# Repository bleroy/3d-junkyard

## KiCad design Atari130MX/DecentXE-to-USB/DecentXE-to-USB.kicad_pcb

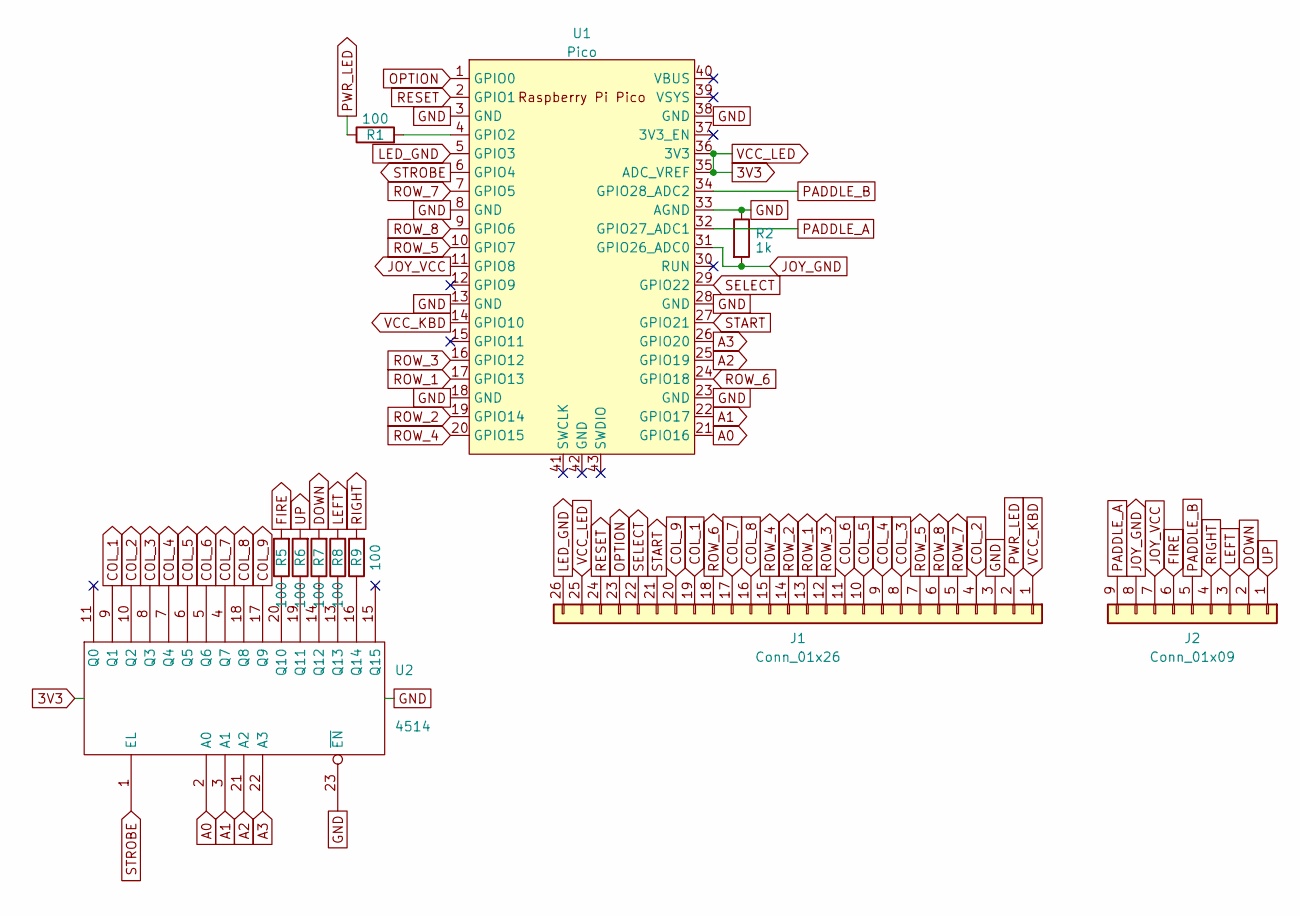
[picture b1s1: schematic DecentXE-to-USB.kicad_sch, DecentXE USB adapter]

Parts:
J1: Conn_01x26; Molex_200528-0260_1x26-1MP_P1.00mm_Horizontal
J2: Conn_01x09; DSUB-9_Male_Horizontal_P2.77x2.84mm_EdgePinOffset4.94mm_Hou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
R1, R5, R6, R7, R8, R9: 100; R_0603_1608Metric
R2: 1k; R_0603_1608Metric
U1: Pico; RPi_Pico_SMD_TH
U2: 4514; SOIC-24W_7.5x15.4mm_P1.27mm

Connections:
3V3: J1.25, U1.35 (ADC_VREF), U1.36 (3V3), U2.24 (Vdd)
A0: U1.21 (GPIO16), U2.2 (A0)
A1: U1.22 (GPIO17), U2.3 (A1)
A2: U1.25 (GPIO19), U2.21 (A2)
A3: U1.26 (GPIO20), U2.22 (A3)
COL_1: J1.19, U2.9 (Q1)
COL_2: J1.4, U2.10 (Q2)
COL_3: J1.8, U2.8 (Q3)
COL_4: J1.9, U2.7 (Q4)
COL_5: J1.10, U2.6 (Q5)
COL_6: J1.11, U2.5 (Q6)
COL_7: J1.17, U2.4 (Q7)
COL_8: J1.16, U2.18 (Q8)
COL_9: J1.20, U2.17 (Q9)
DOWN: J2.2, R7.2
FIRE: J2.6, R5.2
GND: J1.3, R2.1, U1.3 (GND), U1.8 (GND), U1.13 (GND), U1.18 (GND), U1.23 (GND), U1.28 (GND), U1.33 (AGND), U1.38 (GND), U2.12 (Vss), U2.23 (~EN)
JOY_GND: J2.8, R2.2, U1.31 (GPIO26_ADC0)
JOY_VCC: J2.7, U1.11 (GPIO8)
LED_GND: J1.26, U1.5 (GPIO3)
LEFT: J2.3, R8.2
unnamed: R1.2, U1.4 (GPIO2)
unnamed: R5.1, U2.20 (Q10)
unnamed: R6.1, U2.19 (Q11)
unnamed: R7.1, U2.14 (Q12)
unnamed: R8.1, U2.13 (Q13)
unnamed: R9.1, U2.16 (Q14)
OPTION: J1.23, U1.1 (GPIO0)
PADDLE_A: J2.9, U1.32 (GPIO27_ADC1)
PADDLE_B: J2.5, U1.34 (GPIO28_ADC2)
PWR_LED: J1.2, R1.1
RESET: J1.24, U1.2 (GPIO1)
RIGHT: J2.4, R9.2
ROW_1: J1.13, U1.17 (GPIO13)
ROW_2: J1.14, U1.19 (GPIO14)
ROW_3: J1.12, U1.16 (GPIO12)
ROW_4: J1.15, U1.20 (GPIO15)
ROW_5: J1.7, U1.10 (GPIO7)
ROW_6: J1.18, U1.24 (GPIO18)
ROW_7: J1.5, U1.7 (GPIO5)
ROW_8: J1.6, U1.9 (GPIO6)
SELECT: J1.22, U1.29 (GPIO22)
START: J1.21, U1.27 (GPIO21)
STROBE: U1.6 (GPIO4), U2.1 (EL)
UP: J2.1, R6.2
VCC_KBD: J1.1, U1.14 (GPIO10)

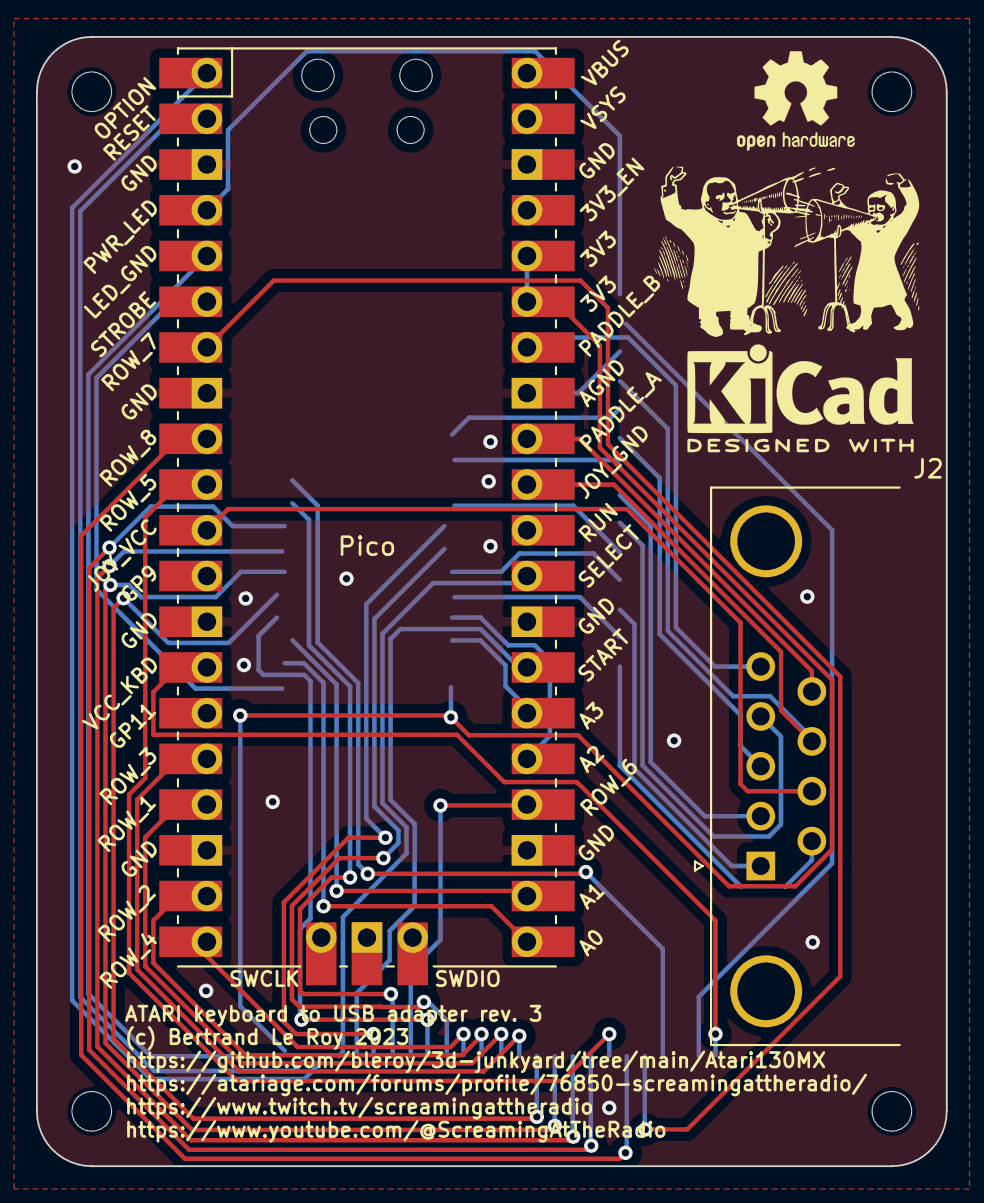
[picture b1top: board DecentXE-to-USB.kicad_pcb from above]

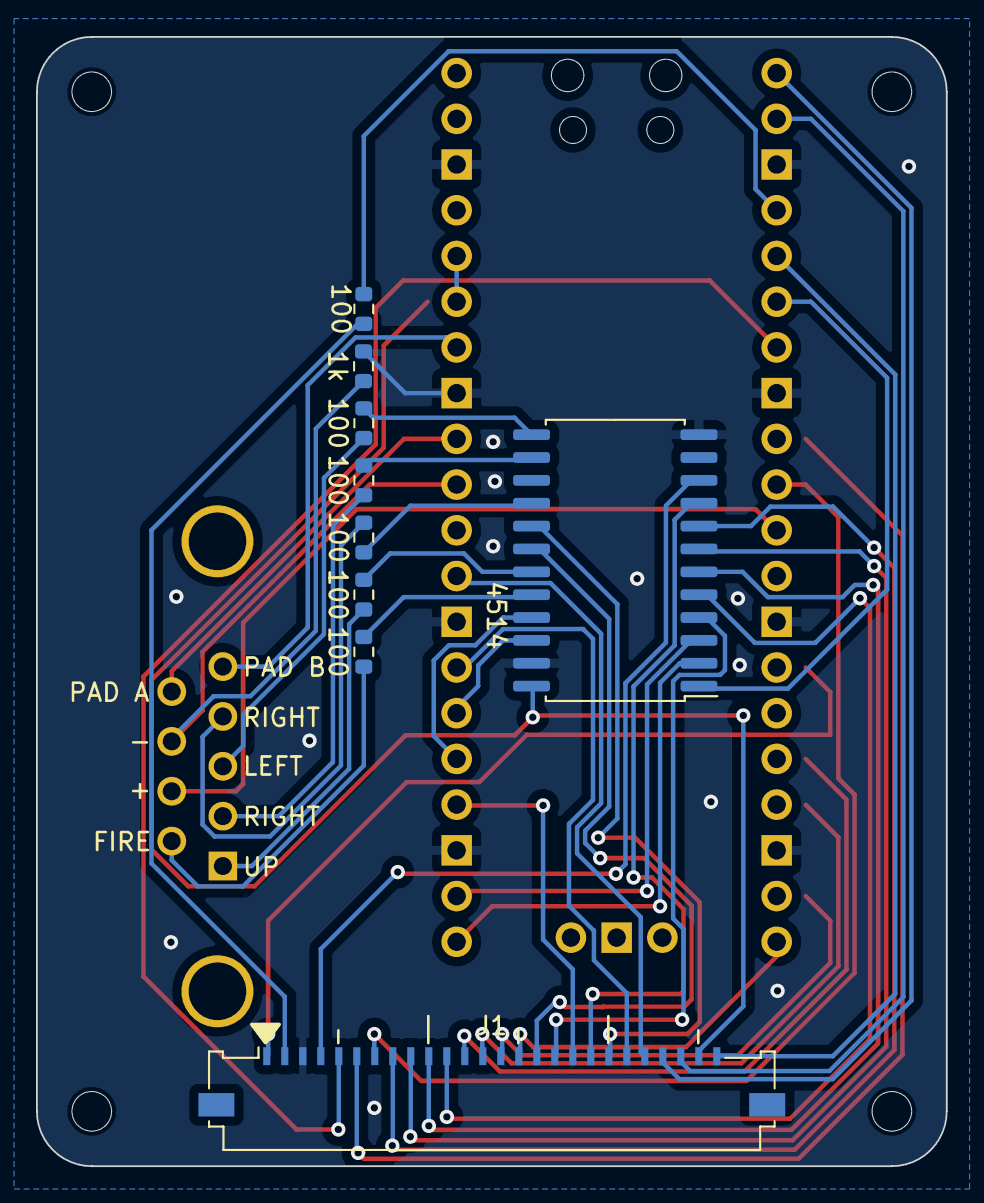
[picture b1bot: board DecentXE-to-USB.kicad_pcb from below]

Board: 2 copper layers, 50.5 x 62.7 mm, 11 parts (9 on the bottom side), 46 nets.

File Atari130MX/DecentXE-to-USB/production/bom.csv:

Designator,Footprint,Quantity,Value,LCSC Part #,Fitted
J1,Molex_200528-0260_1x26-1MP_P1.00mm_Horizontal,1,Conn_01x26,C60248,Y
J2,DSUB-9_Male_Horizontal_P2.77x2.84mm_EdgePinOffset4.94mm_Housed_MountingHolesOffset7.48mm,1,Conn_01x09,,N
"R1, R5, R6, R7, R8, R9",0603,6,100,C22775,Y
R2,0603,1,1k,C2765616,Y
U1,RPi_Pico_SMD_TH,1,Pico,,N
U2,SOIC-24W_7.5x15.4mm_P1.27mm,1,4514,C496122,Y

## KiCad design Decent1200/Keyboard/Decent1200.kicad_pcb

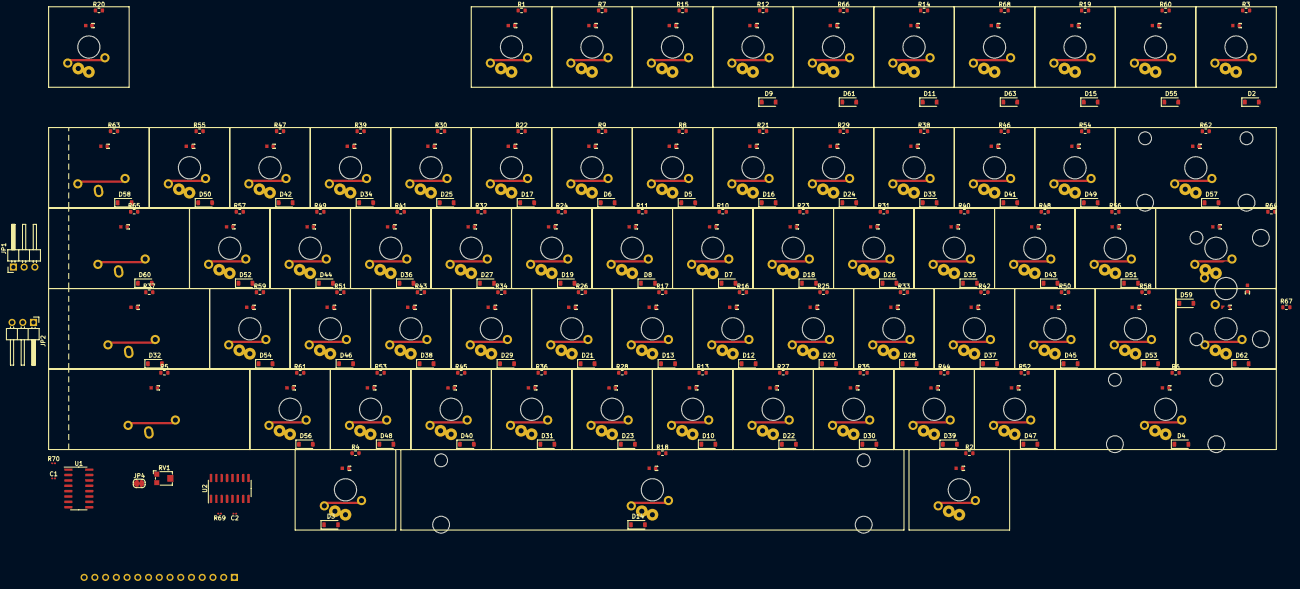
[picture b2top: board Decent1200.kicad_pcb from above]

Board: 2 copper layers, 210 parts (1 on the bottom side), 164 nets, no tracks yet.

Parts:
C1, C2: 100nF; C_0201_0603Metric
D2, D3, D4, D5, D6, D7, D8, D9, D10, D11, D12, D13, D14, D15, D16, D17, D18, D19, D20, D21, D22, D23, D24, D25, D26, D27, D28, D29, D30, D31, D32, D33, D34, D35, D36, D37, D38, D39, D40, D41, D42, D43, D44, D45, D46, D47, D48, D49, D50, D51, D52, D53, D54, D55, D56, D57, D58, D59, D60, D61, D62, D63: 1N4148W; D_SOD-123
J1: Conn_01x15; PinHeader_1x15_P2.54mm_Horizontal
JP1, JP2: Jumper_3_Bridged12; PinHeader_1x03_P2.54mm_Horizontal
JP4: SolderJumper_2_Bridged; SolderJumper-2_P1.3mm_Bridged_RoundedPad1.0x1.5mm
R1, R2, R3, R4, R5, R6, R7, R8, R9, R10, R11, R12, R13, R14, R15, R16, R17, R18, R19, R20, R21, R22, R23, R24, R25, R26, R27, R28, R29, R30, R31, R32, R33, R34, R35, R36, R37, R38, R39, R40, R41, R42, R43, R44, R45, R46, R47, R48, R49, R50, R51, R52, R53, R54, R55, R56, R57, R58, R59, R60, R61, R62, R63, R64, R65, R66, R67, R68: R; R_0603_1608Metric
R69, R70: 4k7; R_0201_0603Metric
RV1: R_Potentiometer; Potentiometer_Bourns_TC33X_Vertical
SW0: 0; MX-1-00U-LED
SW1: 1; MX-1-00U-LED
SW2: 2; MX-1-00U-LED
SW3: 3; MX-1-00U-LED
SW4: 4; MX-1-00U-LED
SW5: 5; MX-1-00U-LED
SW6: 6; MX-1-00U-LED
SW7: 7; MX-1-00U-LED
SW8: 8; MX-1-00U-LED
SW9: 9; MX-1-00U-LED
SWA1: A; MX-1-00U-LED
SWB1: B; MX-1-00U-LED
SWBrk1: Break; MX-1-00U-LED
SWC1: C; MX-1-00U-LED
SWComma1: Comma; MX-1-00U-LED
SWCps1: Caps; MX-1-25U-LED
SWCtl1, SWCtl2: Control; MX-1-25U-LED
SWCtlCaps1: ControlCaps; MX-1-75_2-00U-LED
SWD1: D; MX-1-00U-LED
SWDash1: Dash; MX-1-00U-LED
SWDel2: Delete; MX-2-00U-LED
SWE1: E; MX-1-00U-LED
SWEqual1: Equal; MX-1-00U-LED
SWEsc1: Esc; MX-1-00_1-25U-LED
SWF1: F; MX-1-00U-LED
SWFn1: F1; MX-1-00U-LED
SWFn2: F2; MX-1-00U-LED
SWFn3: F3; MX-1-00U-LED
SWFn4: F4; MX-1-00U-LED
SWG1: G; MX-1-00U-LED
SWGT1: >; MX-1-00U-LED
SWH1: H; MX-1-00U-LED
SWHlp1: Help; MX-1-00U-LED
SWI1: I; MX-1-00U-LED
SWInv1: Inverse; MX-1-00U-LED
SWJ1: J; MX-1-00U-LED
SWK1: K; MX-1-00U-LED
SWL1: L; MX-1-00U-LED
SWLT1: <; MX-1-00U-LED
SWLeftSft1: Shift; MX-2-25_2-50U-LED
SWM1: M; MX-1-00U-LED
SWN1: N; MX-1-00U-LED
SWO1: O; MX-1-00U-LED
SWOption1: Option; MX-1-00U-LED
SWP1: P; MX-1-00U-LED
SWPeriod1: Period; MX-1-00U-LED
SWPlus1: Plus; MX-1-00U-LED
SWQ1: Q; MX-1-00U-LED
SWR1: R; MX-1-00U-LED
SWReset1: Reset; MX-1-00U-LED
SWRet1: Return; MX-ISO-RETURN-LED
SWRet2: Return; MX-1-50U-LED
SWRightSft1: Shift; MX-2-75U-LED
SWS1: S; MX-1-00U-LED
SWSelect1: Select; MX-1-00U-LED
SWSemi1: Semicolon; MX-1-00U-LED
SWSlash1: Slash; MX-1-00U-LED
SWSpc1: Space; MX-6-25U-LED
SWStar1: Star; MX-1-00U-LED
SWStart1: Start; MX-1-00U-LED
SWT1: T; MX-1-00U-LED
SWTab1: Tab; MX-1-50_1-75U-LED
SWU1: U; MX-1-00U-LED
SWV1: V; MX-1-00U-LED
SWW1: W; MX-1-00U-LED
SWX1: X; MX-1-00U-LED
SWY1: Y; MX-1-00U-LED
SWZ1: Z; MX-1-00U-LED
U1, U2: 4051; SOIC-16_3.9x9.9mm_P1.27mm

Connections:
COL_1: J1.1, R70.2, SWBrk1.1, SWCtl1.1, SWCtl2.1, SWLeftSft1.1, SWRightSft1.1
COL_2: SW6.1, SW7.1, SWFn1.1, SWFn3.1, SWN1.1, SWU1.1, SWY1.1, U2.1 (X4)
COL_3: SWH1.1, SWHlp1.1, SWJ1.1, SWSpc1.1, U2.2 (X6)
COL_4: SW5.1, SW8.1, SWB1.1, SWG1.1, SWI1.1, SWK1.1, SWM1.1, SWT1.1, U2.15 (X2)
COL_5: SW4.1, SW9.1, SWComma1.1, SWF1.1, SWL1.1, SWO1.1, SWR1.1, SWV1.1, U2.4 (X7)
COL_6: SW0.1, SW3.1, SWC1.1, SWD1.1, SWE1.1, SWP1.1, SWPeriod1.1, SWSemi1.1, U2.5 (X5)
COL_7: SW2.1, SWDash1.1, SWLT1.1, SWPlus1.1, SWS1.1, SWSlash1.1, SWW1.1, SWX1.1, U2.14 (X1)
COL_8: JP1.1 (A), SW1.1, SWA1.1, SWEqual1.1, SWGT1.1, SWInv1.1, SWQ1.1, SWStar1.1, SWZ1.1, U2.13 (X0)
COL_9: JP1.3 (B), SWCps1.1, SWDel2.1, SWEsc1.1, SWFn2.1, SWFn4.1, SWRet1.1, SWRet2.1, SWTab1.1, U2.12 (X3)
GND: C1.1, C2.1, J1.14, JP4.1 (A), SWOption1.2, SWReset1.2, SWSelect1.2, SWStart1.2, U1.3 (X), U1.6 (Inh), U1.7 (VEE), U1.8 (VSS), U2.6 (Inh), U2.7 (VEE), U2.8 (VSS)
LED_GND: JP4.2 (B), R1.2, R2.2, R3.2, R4.2, R5.2, R6.2, R7.2, R8.2, R9.2, R10.2, R11.2, R12.2, R13.2, R14.2, R15.2, R16.2, R17.2, R18.2, R19.2, R20.2, R21.2, R22.2, R23.2, R24.2, R25.2, R26.2, R27.2, R28.2, R29.2, R30.2, R31.2, R32.2, R33.2, R34.2, R35.2, R36.2, R37.2, R38.2, R39.2, R40.2, R41.2, R42.2, R43.2, R44.2, R45.2, R46.2, R47.2, R48.2, R49.2, R50.2, R51.2, R52.2, R53.2, R54.2, R55.2, R56.2, R57.2, R58.2, R59.2, R60.2, R61.2, R62.2, R63.2, R64.2, R65.2, R66.2, R67.2, R68.2
unnamed: D2.2 (A), SWBrk1.2
unnamed: D3.2 (A), SWCtl1.2, SWCtl2.2
unnamed: D4.2 (A), SWLeftSft1.2, SWRightSft1.2
unnamed: D5.2 (A), SW7.2
unnamed: D6.2 (A), SW6.2
unnamed: D7.2 (A), SWU1.2
unnamed: D8.2 (A), SWY1.2
unnamed: D9.2 (A), SWFn1.2
unnamed: D10.2 (A), SWN1.2
unnamed: D11.2 (A), SWFn3.2
unnamed: D12.2 (A), SWJ1.2
unnamed: D13.2 (A), SWH1.2
unnamed: D14.2 (A), SWSpc1.2
unnamed: D15.2 (A), SWHlp1.2
unnamed: D16.2 (A), SW8.2
unnamed: D17.2 (A), SW5.2
unnamed: D18.2 (A), SWI1.2
unnamed: D19.2 (A), SWT1.2
unnamed: D20.2 (A), SWK1.2
unnamed: D21.2 (A), SWG1.2
unnamed: D22.2 (A), SWM1.2
unnamed: D23.2 (A), SWB1.2
unnamed: D24.2 (A), SW9.2
unnamed: D25.2 (A), SW4.2
unnamed: D26.2 (A), SWO1.2
unnamed: D27.2 (A), SWR1.2
unnamed: D28.2 (A), SWL1.2
unnamed: D29.2 (A), SWF1.2
unnamed: D30.2 (A), SWComma1.2
unnamed: D31.2 (A), SWV1.2
unnamed: D32.2 (A), SWCtlCaps1.2
unnamed: D32.1 (K), JP2.2 (C)
unnamed: D33.2 (A), SW0.2
unnamed: D34.2 (A), SW3.2
unnamed: D35.2 (A), SWP1.2
unnamed: D36.2 (A), SWE1.2
unnamed: D37.2 (A), SWSemi1.2
unnamed: D38.2 (A), SWD1.2
unnamed: D39.2 (A), SWPeriod1.2
unnamed: D40.2 (A), SWC1.2
unnamed: D41.2 (A), SWLT1.2
unnamed: D42.2 (A), SW2.2
unnamed: D43.2 (A), SWDash1.2
unnamed: D44.2 (A), SWW1.2
unnamed: D45.2 (A), SWPlus1.2
unnamed: D46.2 (A), SWS1.2
unnamed: D47.2 (A), SWSlash1.2
unnamed: D48.2 (A), SWX1.2
unnamed: D49.2 (A), SWGT1.2
unnamed: D50.2 (A), SW1.2
unnamed: D51.2 (A), SWEqual1.2
unnamed: D52.2 (A), SWQ1.2
unnamed: D53.2 (A), SWStar1.2
unnamed: D54.2 (A), SWA1.2
unnamed: D55.2 (A), SWInv1.2
unnamed: D56.2 (A), SWZ1.2
unnamed: D57.2 (A), SWDel2.2
unnamed: D58.2 (A), SWEsc1.2
unnamed: D59.2 (A), SWRet1.2, SWRet2.2
unnamed: D60.2 (A), SWTab1.2
unnamed: D61.2 (A), SWFn2.2
unnamed: D62.2 (A), SWCps1.2
unnamed: D63.2 (A), SWFn4.2
unnamed: J1.3, R69.2, U2.3 (X)
unnamed: J1.4, U2.11 (A)
unnamed: J1.5, U2.10 (B)
unnamed: J1.6, U2.9 (C)
unnamed: J1.7, U1.11 (A)
unnamed: J1.8, U1.10 (B)
unnamed: J1.9, U1.9 (C)
unnamed: JP1.2 (C), SWCtlCaps1.1
unnamed: R1.1, SWStart1.3
unnamed: R2.1, SWCtl2.3
unnamed: R3.1, SWBrk1.3
unnamed: R4.1, SWCtl1.3
unnamed: R5.1, SWLeftSft1.3
unnamed: R6.1, SWRightSft1.3
unnamed: R7.1, SWSelect1.3
unnamed: R8.1, SW7.3
unnamed: R9.1, SW6.3
unnamed: R10.1, SWU1.3
unnamed: R11.1, SWY1.3
unnamed: R12.1, SWFn1.3
unnamed: R13.1, SWN1.3
unnamed: R14.1, SWFn3.3
unnamed: R15.1, SWOption1.3
unnamed: R16.1, SWJ1.3
unnamed: R17.1, SWH1.3
unnamed: R18.1, SWSpc1.3
unnamed: R19.1, SWHlp1.3
unnamed: R20.1, SWReset1.3
unnamed: R21.1, SW8.3
unnamed: R22.1, SW5.3
unnamed: R23.1, SWI1.3
unnamed: R24.1, SWT1.3
unnamed: R25.1, SWK1.3
unnamed: R26.1, SWG1.3
unnamed: R27.1, SWM1.3
unnamed: R28.1, SWB1.3
unnamed: R29.1, SW9.3
unnamed: R30.1, SW4.3
unnamed: R31.1, SWO1.3
unnamed: R32.1, SWR1.3
unnamed: R33.1, SWL1.3
unnamed: R34.1, SWF1.3
unnamed: R35.1, SWComma1.3
unnamed: R36.1, SWV1.3
unnamed: R37.1, SWCtlCaps1.3
unnamed: R38.1, SW0.3
unnamed: R39.1, SW3.3
unnamed: R40.1, SWP1.3
unnamed: R41.1, SWE1.3
unnamed: R42.1, SWSemi1.3
unnamed: R43.1, SWD1.3
unnamed: R44.1, SWPeriod1.3
unnamed: R45.1, SWC1.3
unnamed: R46.1, SWLT1.3
unnamed: R47.1, SW2.3
unnamed: R48.1, SWDash1.3
unnamed: R49.1, SWW1.3
unnamed: R50.1, SWPlus1.3
unnamed: R51.1, SWS1.3
unnamed: R52.1, SWSlash1.3
unnamed: R53.1, SWX1.3
unnamed: R54.1, SWGT1.3
unnamed: R55.1, SW1.3
unnamed: R56.1, SWEqual1.3
unnamed: R57.1, SWQ1.3
unnamed: R58.1, SWStar1.3
unnamed: R59.1, SWA1.3
unnamed: R60.1, SWInv1.3
unnamed: R61.1, SWZ1.3
unnamed: R62.1, SWDel2.3
unnamed: R63.1, SWEsc1.3
unnamed: R64.1, SWRet2.3
unnamed: R65.1, SWTab1.3
unnamed: R66.1, SWFn2.3
unnamed: R67.1, SWCps1.3
unnamed: R68.1, SWFn4.3
OPTION: J1.13, SWOption1.1
RESET: J1.10, SWReset1.1
ROW_1: D2.1 (K), D5.1 (K), D16.1 (K), D24.1 (K), D33.1 (K), D41.1 (K), D49.1 (K), D57.1 (K), U1.14 (X1)
ROW_2: D6.1 (K), D17.1 (K), D25.1 (K), D34.1 (K), D42.1 (K), D50.1 (K), D58.1 (K), U1.1 (X4)
ROW_3: D7.1 (K), D18.1 (K), D26.1 (K), D35.1 (K), D43.1 (K), D51.1 (K), D59.1 (K), U1.2 (X6)
ROW_4: D8.1 (K), D19.1 (K), D27.1 (K), D36.1 (K), D44.1 (K), D52.1 (K), D60.1 (K), U1.15 (X2)
ROW_5: D3.1 (K), D9.1 (K), D12.1 (K), D20.1 (K), D28.1 (K), D37.1 (K), D45.1 (K), D53.1 (K), D61.1 (K), JP2.1 (A), U1.4 (X7)
ROW_6: D13.1 (K), D21.1 (K), D29.1 (K), D38.1 (K), D46.1 (K), D54.1 (K), D62.1 (K), JP2.3 (B), U1.13 (X0)
ROW_7: D10.1 (K), D14.1 (K), D22.1 (K), D30.1 (K), D39.1 (K), D47.1 (K), D55.1 (K), U1.12 (X3)
ROW_8: D4.1 (K), D11.1 (K), D15.1 (K), D23.1 (K), D31.1 (K), D40.1 (K), D48.1 (K), D56.1 (K), D63.1 (K), U1.5 (X5)
SELECT: J1.12, SWSelect1.1
START: J1.11, SWStart1.1
VCC_LED: RV1.1, SW0.4, SW1.4, SW2.4, SW3.4, SW4.4, SW5.4, SW6.4, SW7.4, SW8.4, SW9.4, SWA1.4, SWB1.4, SWBrk1.4, SWC1.4, SWComma1.4, SWCps1.4, SWCtl1.4, SWCtl2.4, SWCtlCaps1.4, SWD1.4, SWDash1.4, SWDel2.4, SWE1.4, SWEqual1.4, SWEsc1.4, SWF1.4, SWFn1.4, SWFn2.4, SWFn3.4, SWFn4.4, SWG1.4, SWGT1.4, SWH1.4, SWHlp1.4, SWI1.4, SWInv1.4, SWJ1.4, SWK1.4, SWL1.4, SWLT1.4, SWLeftSft1.4, SWM1.4, SWN1.4, SWO1.4, SWOption1.4, SWP1.4, SWPeriod1.4, SWPlus1.4, SWQ1.4, SWR1.4, SWReset1.4, SWRet2.4, SWRightSft1.4, SWS1.4, SWSelect1.4, SWSemi1.4, SWSlash1.4, SWSpc1.4, SWStar1.4, SWStart1.4, SWT1.4, SWTab1.4, SWU1.4, SWV1.4, SWW1.4, SWX1.4, SWY1.4, SWZ1.4
VDD: C1.2, C2.2, J1.15, R69.1, R70.1, RV1.2, U1.16 (VDD), U2.16 (VDD)

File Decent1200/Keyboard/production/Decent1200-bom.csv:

Designator,Footprint,Quantity,Value,LCSC Part #
"C1, C2",0603,2,100nF,C14663
"D10, D11, D12, D13, D14, D15, D16, D17, D18, D19, D2, D20, D21, D22, D23, D24, D25, D26, D27, D28, D29, D3, D30, D31, D32, D33, D34, D35, D36, D37, D38, D39, D4, D40, D41, D42, D43, D44, D45, D46, D47, D48, D49, D5, D50, D51, D52, D53, D54, D55, D56, D57, D58, D59, D6, D60, D61, D62, D63, D7, D8, D9",D_SOD-123,62,1N4148W,C81598
J1,PinHeader_1x15_P2.54mm_Horizontal,1,Conn_01x15,
"JP1, JP2",PinHeader_1x03_P2.54mm_Horizontal,2,Jumper_3_Bridged12,
JP4,SolderJumper-2_P1.3mm_Bridged_RoundedPad1.0x1.5mm,1,SolderJumper_2_Bridged,
"R1, R10, R11, R12, R13, R14, R15, R16, R17, R18, R19, R2, R20, R21, R22, R23, R24, R25, R26, R27, R28, R29, R3, R30, R31, R32, R33, R34, R35, R36, R37, R38, R39, R4, R40, R41, R42, R43, R44, R45, R46, R47, R48, R49, R5, R50, R51, R52, R53, R54, R55, R56, R57, R58, R59, R6, R60, R61, R62, R63, R64, R65, R66, R67, R68, R7, R8, R9",0603,68,R, C22775
"R69, R70",0603,2,4k7,C23162
RV1,Potentiometer_Bourns_TC33X_Vertical,1,R_Potentiometer,C720647
SW0,MX-1-00U-LED,1,0,C193191
SW1,MX-1-00U-LED,1,1,C193191
SW2,MX-1-00U-LED,1,2,C193191
SW3,MX-1-00U-LED,1,3,C193191
SW4,MX-1-00U-LED,1,4,C193191
SW5,MX-1-00U-LED,1,5,C193191
SW6,MX-1-00U-LED,1,6,C193191
SW7,MX-1-00U-LED,1,7,C193191
SW8,MX-1-00U-LED,1,8,C193191
SW9,MX-1-00U-LED,1,9,C193191
SWA1,MX-1-00U-LED,1,A,C193191
SWB1,MX-1-00U-LED,1,B,C193191
SWBrk1,MX-1-00U-LED,1,Break,C193191
SWC1,MX-1-00U-LED,1,C,C193191
SWComma1,MX-1-00U-LED,1,Comma,C193191
SWCps1,MX-1-25U-CAPS-LED,1,Caps,C193191
"SWCtl1, SWCtl2",MX-1-25U-LED,2,Control,C193191
SWCtlCaps1,MX-1-75_2-00U-LED,1,ControlCaps,C193191
SWD1,MX-1-00U-LED,1,D,C193191
SWDash1,MX-1-00U-LED,1,Dash,C193191
SWDel2,MX-2-00U-LED,1,Delete,C193191
SWE1,MX-1-00U-LED,1,E,C193191
SWEqual1,MX-1-00U-LED,1,Equal,C193191
SWEsc1,MX-1-00_1-25U-LED,1,Esc,C193191
SWF1,MX-1-00U-LED,1,F,C193191
SWFn1,MX-1-00U-LED,1,F1,C193191
SWFn2,MX-1-00U-LED,1,F2,C193191
SWFn3,MX-1-00U-LED,1,F3,C193191
SWFn4,MX-1-00U-LED,1,F4,C193191
SWG1,MX-1-00U-LED,1,G,C193191
SWGT1,MX-1-00U-LED,1,>,C193191
SWH1,MX-1-00U-LED,1,H,C193191
SWHlp1,MX-1-00U-LED,1,Help,C193191
SWI1,MX-1-00U-LED,1,I,C193191
SWInv1,MX-1-00U-LED,1,Inverse,C193191
SWJ1,MX-1-00U-LED,1,J,C193191
SWK1,MX-1-00U-LED,1,K,C193191
SWL1,MX-1-00U-LED,1,L,C193191
SWLT1,MX-1-00U-LED,1,<,C193191
SWLeftSft1,MX-2-25_2-50U-LED,1,Shift,C193191
SWM1,MX-1-00U-LED,1,M,C193191
SWN1,MX-1-00U-LED,1,N,C193191
SWO1,MX-1-00U-LED,1,O,C193191
SWOption1,MX-1-00U-LED,1,Option,C193191
SWP1,MX-1-00U-LED,1,P,C193191
SWPeriod1,MX-1-00U-LED,1,Period,C193191
SWPlus1,MX-1-00U-LED,1,Plus,C193191
SWQ1,MX-1-00U-LED,1,Q,C193191
SWR1,MX-1-00U-LED,1,R,C193191
SWReset1,MX-1-00U-LED,1,Reset,C193191
SWRet1,MX-ISO-RETURN,1,Return,C193191
SWRet2,MX-1-50U-RETURN-LED,1,Return,C193191
SWRightSft1,MX-2-75U-LED,1,Shift,C193191
SWS1,MX-1-00U-LED,1,S,C193191
SWSelect1,MX-1-00U-LED,1,Select,C193191
SWSemi1,MX-1-00U-LED,1,Semicolon,C193191
SWSlash1,MX-1-00U-LED,1,Slash,C193191
SWSpc1,MX-6-25U-LED,1,Space,C193191
SWStar1,MX-1-00U-LED,1,Star,C193191
SWStart1,MX-1-00U-LED,1,Start,C193191
SWT1,MX-1-00U-LED,1,T,C193191
SWTab1,MX-1-50_1-75U-LED,1,Tab,C193191
SWU1,MX-1-00U-LED,1,U,C193191
SWV1,MX-1-00U-LED,1,V,C193191
SWW1,MX-1-00U-LED,1,W,C193191
SWX1,MX-1-00U-LED,1,X,C193191
SWY1,MX-1-00U-LED,1,Y,C193191
SWZ1,MX-1-00U-LED,1,Z,C193191
"U1, U2",SOIC-16_3.9x9.9mm_P1.27mm,2,4051,C21379
